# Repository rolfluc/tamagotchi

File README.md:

# tamagotchi
SW/
Contains the associated software for the project
EE/
Contains the respective electrical aspects
Mechanical/
Contains the mechanical bits.

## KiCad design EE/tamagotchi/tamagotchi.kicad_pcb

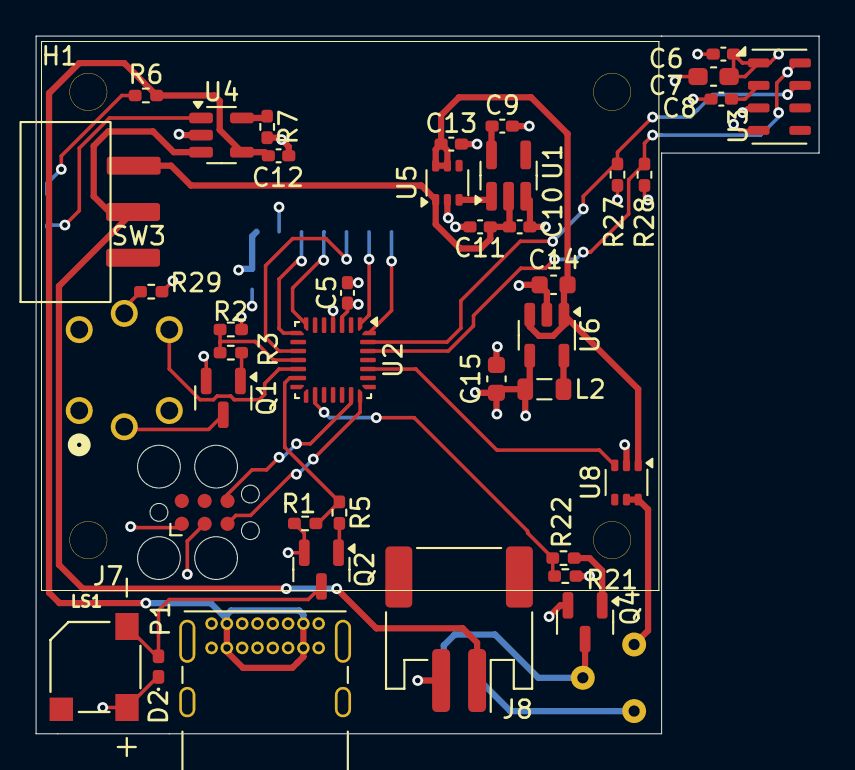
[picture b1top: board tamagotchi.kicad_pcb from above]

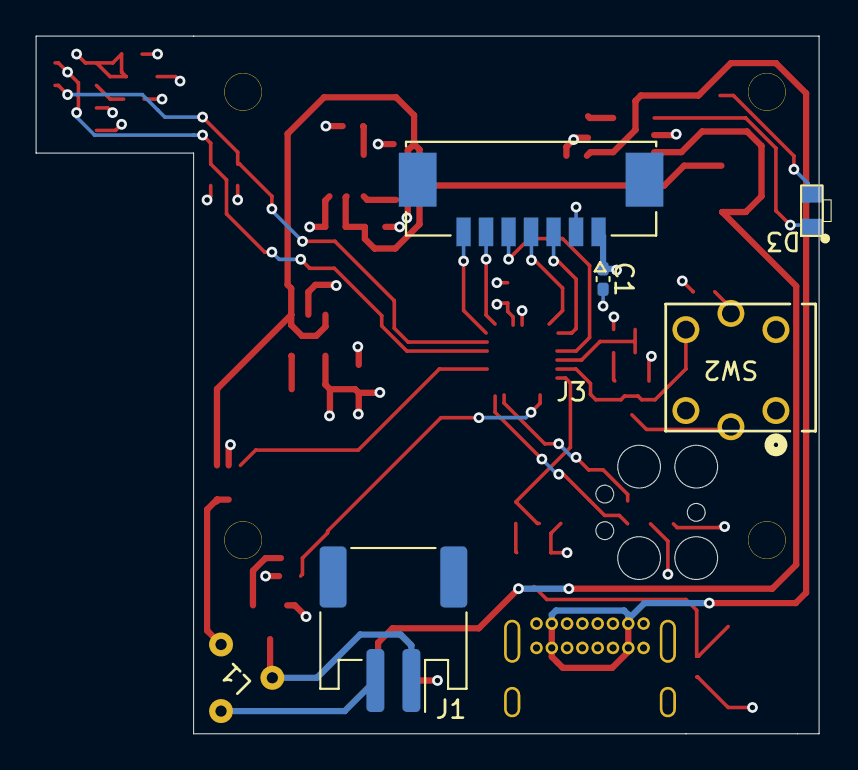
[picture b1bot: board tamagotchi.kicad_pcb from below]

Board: 4 copper layers, 43.5 x 38.8 mm, 46 parts (6 on the bottom side), 36 nets.

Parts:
C1, C5, C6, C8, C11: 0.1u; C_0402_1005Metric_Pad0.74x0.62mm_HandSolder
C7: 10u; C_0603_1608Metric_Pad1.08x0.95mm_HandSolder
C9, C10, C12, C13: 1u; C_0402_1005Metric_Pad0.74x0.62mm_HandSolder
C14, C15: 4.7u; C_0603_1608Metric
D2: D; D_0402_1005Metric_Pad0.77x0.64mm_HandSolder
D3: LED; LED_0604
H1: ScreenMount
J1, J8: Conn_01x02_Male; JST_PH_S2B-PH-SM4-TB_1x02-1MP_P2.00mm_Horizontal
J3: Conn_01x07; MOLEX_532610771
J7: TAG_CONNECT; Tag-Connect_TC2030-IDC-FP_2x03_P1.27mm_Vertical
L1: UT Transformer
L2: 4.7u; L_0805_2012Metric
LS1: SMT-0540-T-10-R; XDCR_SMT-0540-T-10-R
P1: USB_C_Plug_USB2.0; USB_C_Receptacle_GCT_USB4085
Q1, Q2, Q4: Q_NMOS_GSD; SOT-23
R1: 100k; R_0402_1005Metric_Pad0.72x0.64mm_HandSolder
R2, R21: 10k; R_0402_1005Metric_Pad0.72x0.64mm_HandSolder
R3, R5, R22: 33; R_0402_1005Metric_Pad0.72x0.64mm_HandSolder
R6, R7: 3.3k; R_0402_1005Metric_Pad0.72x0.64mm_HandSolder
R27, R28: 4.7k; R_0402_1005Metric_Pad0.72x0.64mm_HandSolder
R29: 1k; R_0402_1005Metric_Pad0.72x0.64mm_HandSolder
SW2: TL1260BQRBLK; TL1260_EWI
SW3: SW_SPDT_321; EGJ1210
U1: TPS3840PL30DBVR; SC-74A-5_1.55x2.9mm_P0.95mm
U2: STM32G031G8Ux; QFN-28_4x4mm_P0.5mm
U3: MPL3115A2; NXP_LGA-8_3x5mm_P1.25mm_H1.1mm
U4: STC4054GR; TSOT-23-5
U5, U8: TPS22919QDCKRQ1; SOT-363_SC-70-6
U6: LM3670MF-3.3/NOPB; TSOT-23-5

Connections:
+3V3: C1.1, C5.1, C6.1, C7.1, C15.1, D2.1 (K), J3.1, J7.1 (POWER_3V3), L2.2, LS1.P, R27.1, R28.1, R29.1, U2.3 (VDD), U3.1 (VDD), U3.4 (VDDIO), U6.4 (FB)
/Display/BUZZ_PWM: R1.1, R5.1, U2.13 (PA7)
/Display/CLK: J3.4, U2.7 (PA1)
/Display/CS: J3.5, U2.10 (PA4)
/Display/DC: J3.6, U2.1 (PC14)
/Display/MOSI: J3.3, U2.8 (PA2)
/Display/RST: J3.7, U2.28 (PB8)
/MCU/SWCLK: J7.5 (SWCLK), U2.21 (PA14)
/MCU/SWDIO: J7.6 (SWDIO), U2.20 (PA13)
/MCU/VAPE_EN_N: U2.24 (PB4), U8.3 (ON)
/MCU/VAPE_LED: R2.1, R3.1, U2.11 (PA5)
/MCU/VAPE_PWM: R21.1, R22.1, U2.16 (PA8)
/MCU/VAPE_SW: SW2.4, U2.12 (PA6)
/Power/CT: C9.1, U1.5 (CT)
/Power/MONITOR: U1.1 (RESET_N), U5.3 (ON)
/Power/VBAT: C10.1, C11.1, SW3.3 (A), U1.2 (VDD), U5.1 (VIN)
/Power/VBAT_PRESWITCH: J8.1, SW3.2 (B), U4.3 (BAT)
/SCL: R28.2, U2.26 (PB6), U3.8 (SCL)
/SDA: R27.2, U2.27 (PB7), U3.7 (SDL)
/VBAT: C13.1, C14.1, U5.5 (QOD), U5.6 (VOUT), U6.1 (Vin), U6.3 (EN), U8.1 (VIN)
/Vape/UT_OUT+: J1.2, L1.3 (UT_OUT)
/Vape/UT_OUT-: J1.1, L1.1 (GND), Q4.3 (D)
/Vape/VBAT_CONT: L1.2 (POWER_IN), U8.5 (QOD), U8.6 (VOUT)
GND: C1.2, C5.2, C6.2, C7.2, C8.2, C9.2, C10.2, C11.2, C12.2, C13.2, C14.2, C15.2, J3.2, J7.3 (GND), J8.2, P1.A1 (GND), P1.A12 (GND), P1.B1 (GND), P1.B12 (GND), P1.S1 (SHIELD), Q1.2 (S), Q2.2 (S), Q4.2 (S), R1.2, R2.2, R7.2, R21.2, SW2.1, U1.3 (GND), U2.4 (VSS), U3.3 (GND), U4.2 (GND), U5.2 (GND), U6.2 (GND), U8.2 (GND)
unnamed: D2.2 (A), LS1.N, Q2.3 (D)
unnamed: D3.2 (A), R6.1
unnamed: D3.1 (K), U4.1 (CHRG)
unnamed: Q1.3 (D), SW2.5
unnamed: Q1.1 (G), R3.2
unnamed: Q2.1 (G), R5.2
unnamed: Q4.1 (G), R22.2
unnamed: R29.2, SW2.6
unnamed: C8.1, U3.2 (CAP)
unnamed: R7.1, U4.5 (PROG)
unnamed: L2.1, U6.5 (SW)
VBUS: C12.1, P1.A4 (VBUS), P1.A9 (VBUS), P1.B4 (VBUS), P1.B9 (VBUS), R6.2, U4.4 (VCC)

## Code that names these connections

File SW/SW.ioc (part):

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Mcu.Name=STM32G031G(4-6-8)Ux
Mcu.Package=UFQFPN28
Mcu.UserName=STM32G031G8Ux
PA1.Mode=Simplex_Bidirectional_Master
PA1.Signal=SPI1_SCK
PA13.Mode=Serial_Wire
PA13.Signal=SYS_SWDIO
PA14-BOOT0.Mode=Serial_Wire
PA14-BOOT0.Signal=SYS_SWCLK
PA2.Mode=Simplex_Bidirectional_Master
PA2.Signal=SPI1_MOSI
PA4.Mode=NSS_Signal_Hard_Output
PA4.Signal=SPI1_NSS
PA5.Signal=GPIO_Output
PA6.Signal=GPIO_Output
PA7.Signal=S_TIM3_CH2
PA8.Signal=S_TIM1_CH1
PB6.Mode=I2C
PB6.Signal=I2C1_SCL
PB7.Mode=I2C
PB7.Signal=I2C1_SDA
RCC.HSE_VALUE=8000000
RCC.SYSCLKFreq_VALUE=16000000
board=custom

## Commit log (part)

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2025-06-16 Project Locations Start
2026-01-23 Added first mechanicals, and electrical components
2026-01-25 Generic Continutation Checkin
2026-01-25 Minor Update pre Display add
2026-01-30 Added parts for use
2026-01-30 WIP - added 3D / footprints for devices. RGY LEDs aren't right
    Need to do more outling / ect. super rough placement for everything.
    LED footprint for RGY appears just wrong
2026-01-31 Footprints and mechanical parts assigned
2026-01-31 Basic Placement Complete
2026-01-31 Migrated to 4 Layer. Added 3v3 and gnd layers
2026-01-31 Minor Placement update
2026-02-01 Removed LEDs
2026-02-01 First pass routing / placement & LED -> Buzzer for warning
2026-02-01 Silkscreen Fix
2026-02-01 Fixed board outline
2026-02-01 Adding some new requirements for pressure / air flow
2026-03-19 Added pressure sensor. Re laid out board
2026-03-19 Updated Mechanical Files - Mouthpiec
2026-03-22 Further mechanical Improvements
2026-05-19 Mechanical Change
2026-05-30 Minot Improvements / Cable Routing
